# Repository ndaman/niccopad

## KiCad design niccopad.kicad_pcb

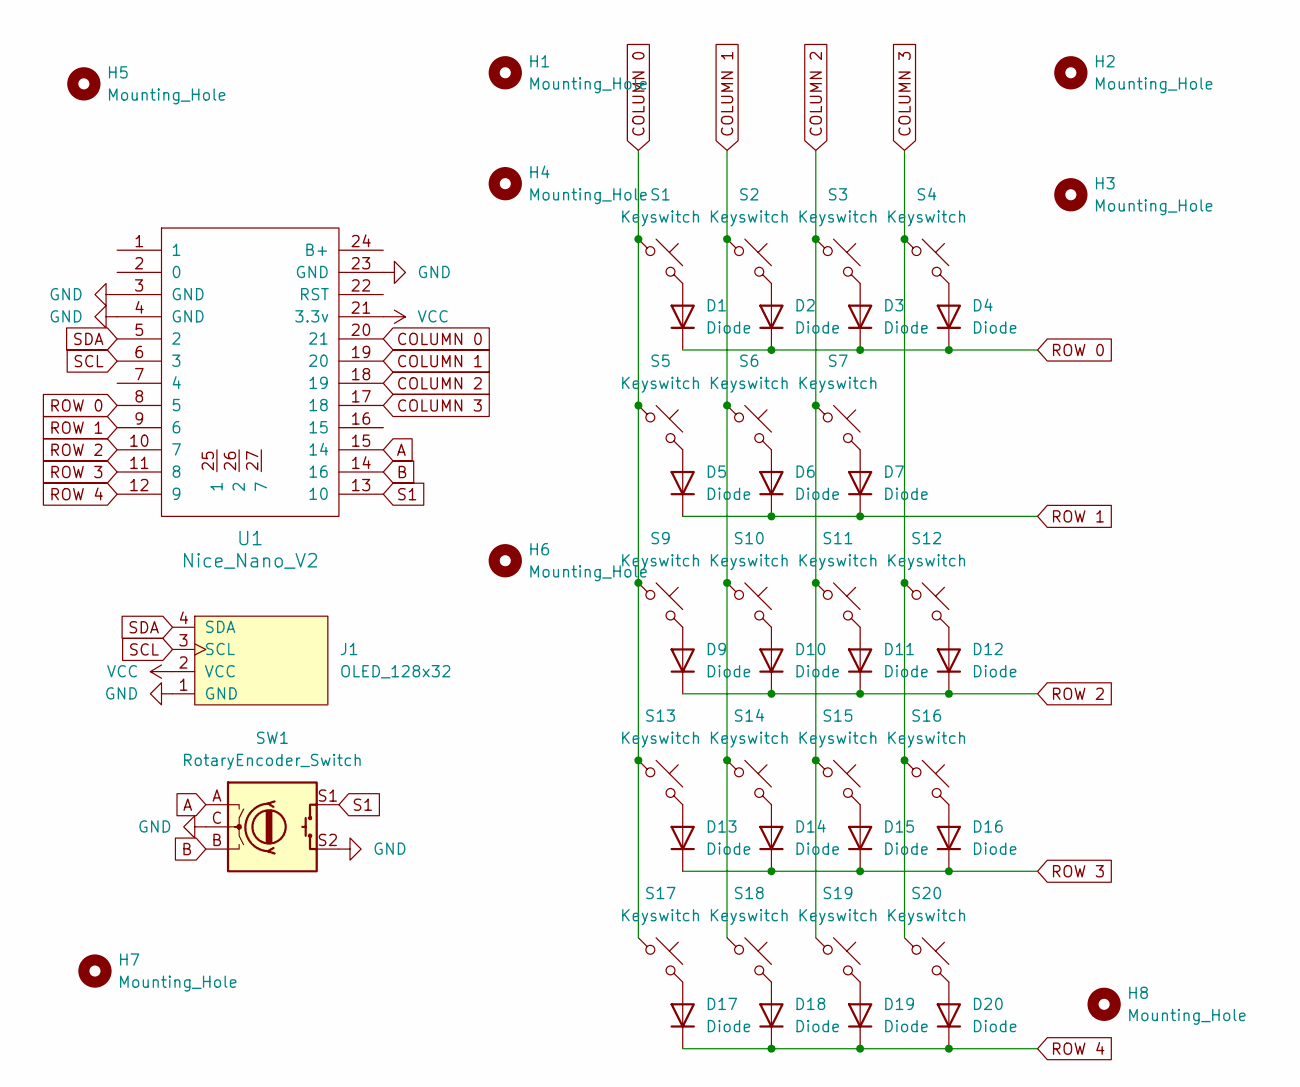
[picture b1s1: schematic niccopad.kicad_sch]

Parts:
D1, D2, D3, D4, D5, D6, D7, D9, D10, D11, D12, D13, D14, D15, D16, D17, D18, D19, D20: Diode; Diode_DO-35
H1, H2, H3, H4, H5, H6, H7, H8: Mounting_Hole
J1: OLED_128x32
S1, S2, S3, S4, S5, S6, S7, S9, S10, S11, S13, S14, S15, S16, S17, S19: Keyswitch; MX_PCB_1.00u
S12, S20: Keyswitch; MX_PCB_2.00u_90deg
S18: Keyswitch; MX_PCB_2.00u
SW1: RotaryEncoder_Switch; Encoder_EC11_MX
U1: Nice_Nano_V2

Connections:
A: SW1.A, U1.15 (14)
B: SW1.B, U1.14 (16)
COLUMN 0: S1.1, S5.1, S9.1, S13.1, S17.1, U1.20 (21)
COLUMN 1: S2.1, S6.1, S10.1, S14.1, S18.1, U1.19 (20)
COLUMN 2: S3.1, S7.1, S11.1, S15.1, S19.1, U1.18 (19)
COLUMN 3: S4.1, S12.1, S16.1, S20.1, U1.17 (18)
GND: J1.1 (GND), SW1.C, SW1.S2, U1.3 (GND), U1.4 (GND), U1.23 (GND)
unnamed: D1.2 (A), S1.2
unnamed: D2.2 (A), S2.2
unnamed: D3.2 (A), S3.2
unnamed: D4.2 (A), S4.2
unnamed: D5.2 (A), S5.2
unnamed: D6.2 (A), S6.2
unnamed: D7.2 (A), S7.2
unnamed: D9.2 (A), S9.2
unnamed: D10.2 (A), S10.2
unnamed: D11.2 (A), S11.2
unnamed: D12.2 (A), S12.2
unnamed: D13.2 (A), S13.2
unnamed: D14.2 (A), S14.2
unnamed: D15.2 (A), S15.2
unnamed: D16.2 (A), S16.2
unnamed: D17.2 (A), S17.2
unnamed: D18.2 (A), S18.2
unnamed: D19.2 (A), S19.2
unnamed: D20.2 (A), S20.2
ROW 0: D1.1 (K), D2.1 (K), D3.1 (K), D4.1 (K), U1.8 (5)
ROW 1: D5.1 (K), D6.1 (K), D7.1 (K), U1.9 (6)
ROW 2: D9.1 (K), D10.1 (K), D11.1 (K), D12.1 (K), U1.10 (7)
ROW 3: D13.1 (K), D14.1 (K), D15.1 (K), D16.1 (K), U1.11 (8)
ROW 4: D17.1 (K), D18.1 (K), D19.1 (K), D20.1 (K), U1.12 (9)
S1: SW1.S1, U1.13 (10)
SCL: J1.3 (SCL), U1.6 (3)
SDA: J1.4 (SDA), U1.5 (2)
VCC: J1.2 (VCC), U1.21 (3.3v)

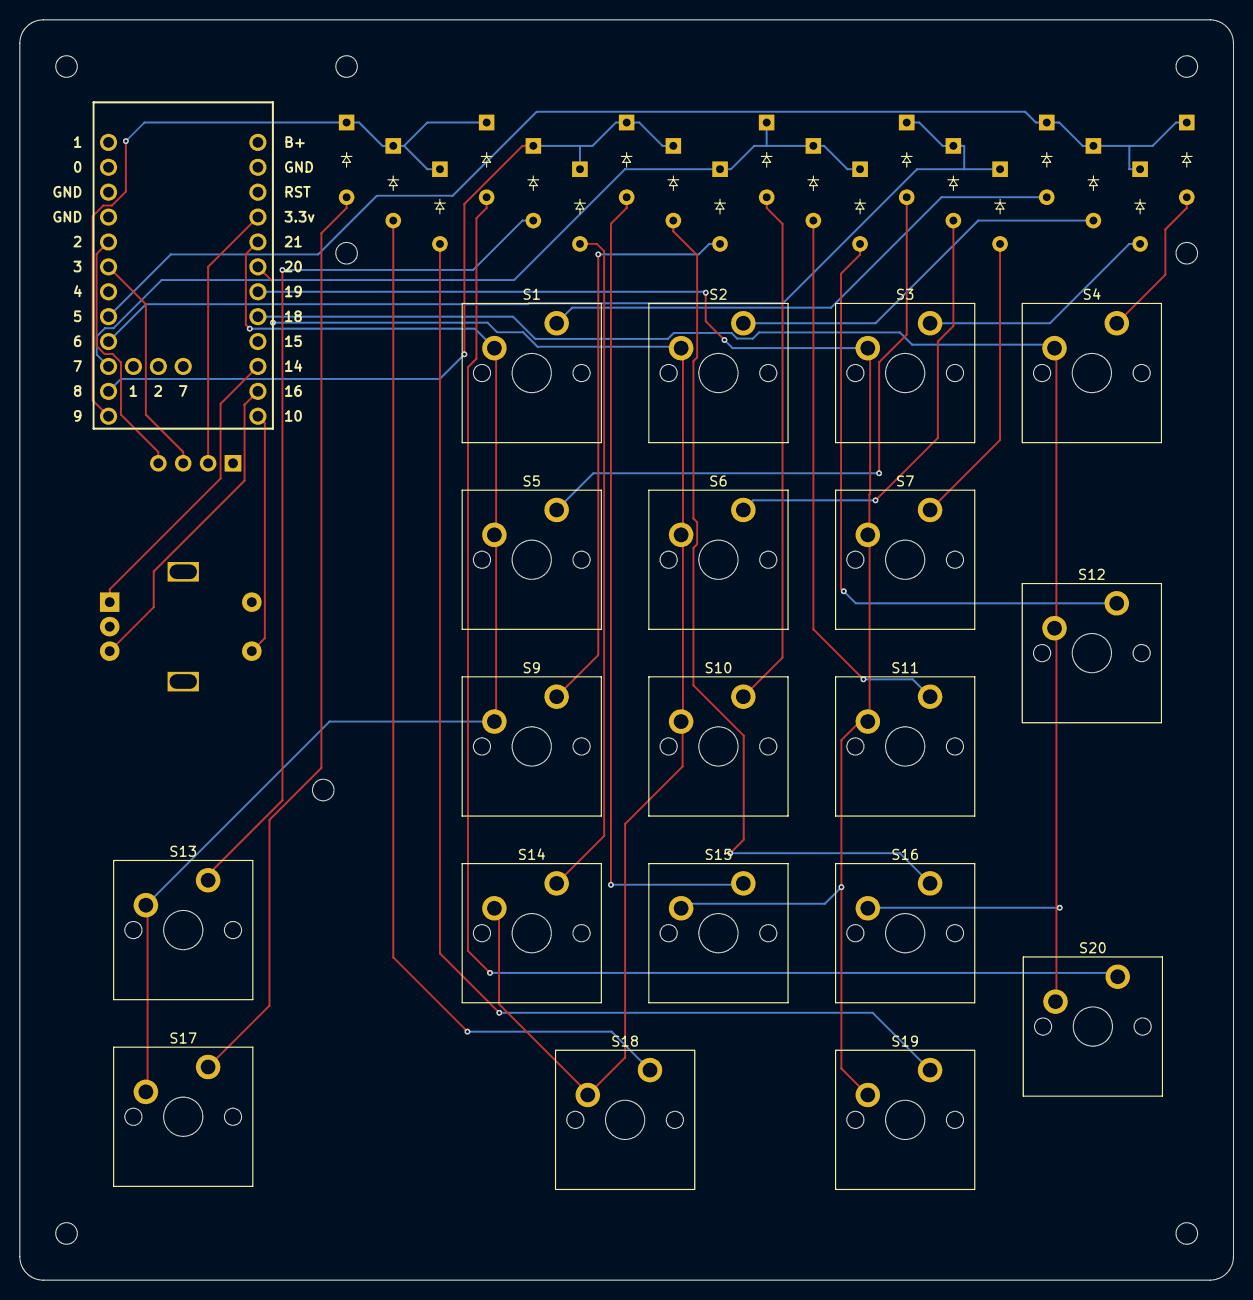
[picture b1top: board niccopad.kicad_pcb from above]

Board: 2 copper layers, 123.8 x 128.6 mm, 49 parts (0 on the bottom side), 35 nets.

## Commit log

2025-06-10 initial re-draw of my macropad
